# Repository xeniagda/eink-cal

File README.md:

# eink-cal

e-ink calendar based on the *esp32-wroom32* and the waveshare *7.3inch e-Paper HAT (F)*

## file structure

* `./bridge_pcb/`: kicad project for the PCB
* `./eink_bridge/`: esp32-idf project for the WiFi-controller for the display
* `./case.FCStd`: freecad project modelling the 3d-printable chassis for the project
* `./cal_render/`: python code to render the calendar

## needed files

the file `./eink_bridge/main/wifi_creds.h` should be filled in with the following

```c

#ifndef wifi_creds_h_INCLUDED
#define wifi_creds_h_INCLUDED

#define WIFI_SSID "WIFI network SSID here"
#define WIFI_PASSWORD "WIFI network password"
static const char *REMOTE_IP = "IP of computer running cal_render";
static const int REMOTE_PORT = port of the above;

#endif // wifi_creds_h_INCLUDED
```

the file `./cal_render/secrets.toml` contains all calendars to be shown

```toml
[[calendar]]
# hemma
is_caldav = true # true for caldav, false for ical/http
username = "caldav username"
password = "caldav password"
url = "caldav URL"
color1 = "primary color" # one of BLACK, WHITE, BLUE, ORANGE, GREEN, RED, PURPLE
color2 = "secondary color"
```

## credits

font packaged and used is [ultlf](https://github.com/ultlang/ultlf) by emma ultlang. all parts of `./cal_render/ultlf` are re-released under the same SIL open font license.

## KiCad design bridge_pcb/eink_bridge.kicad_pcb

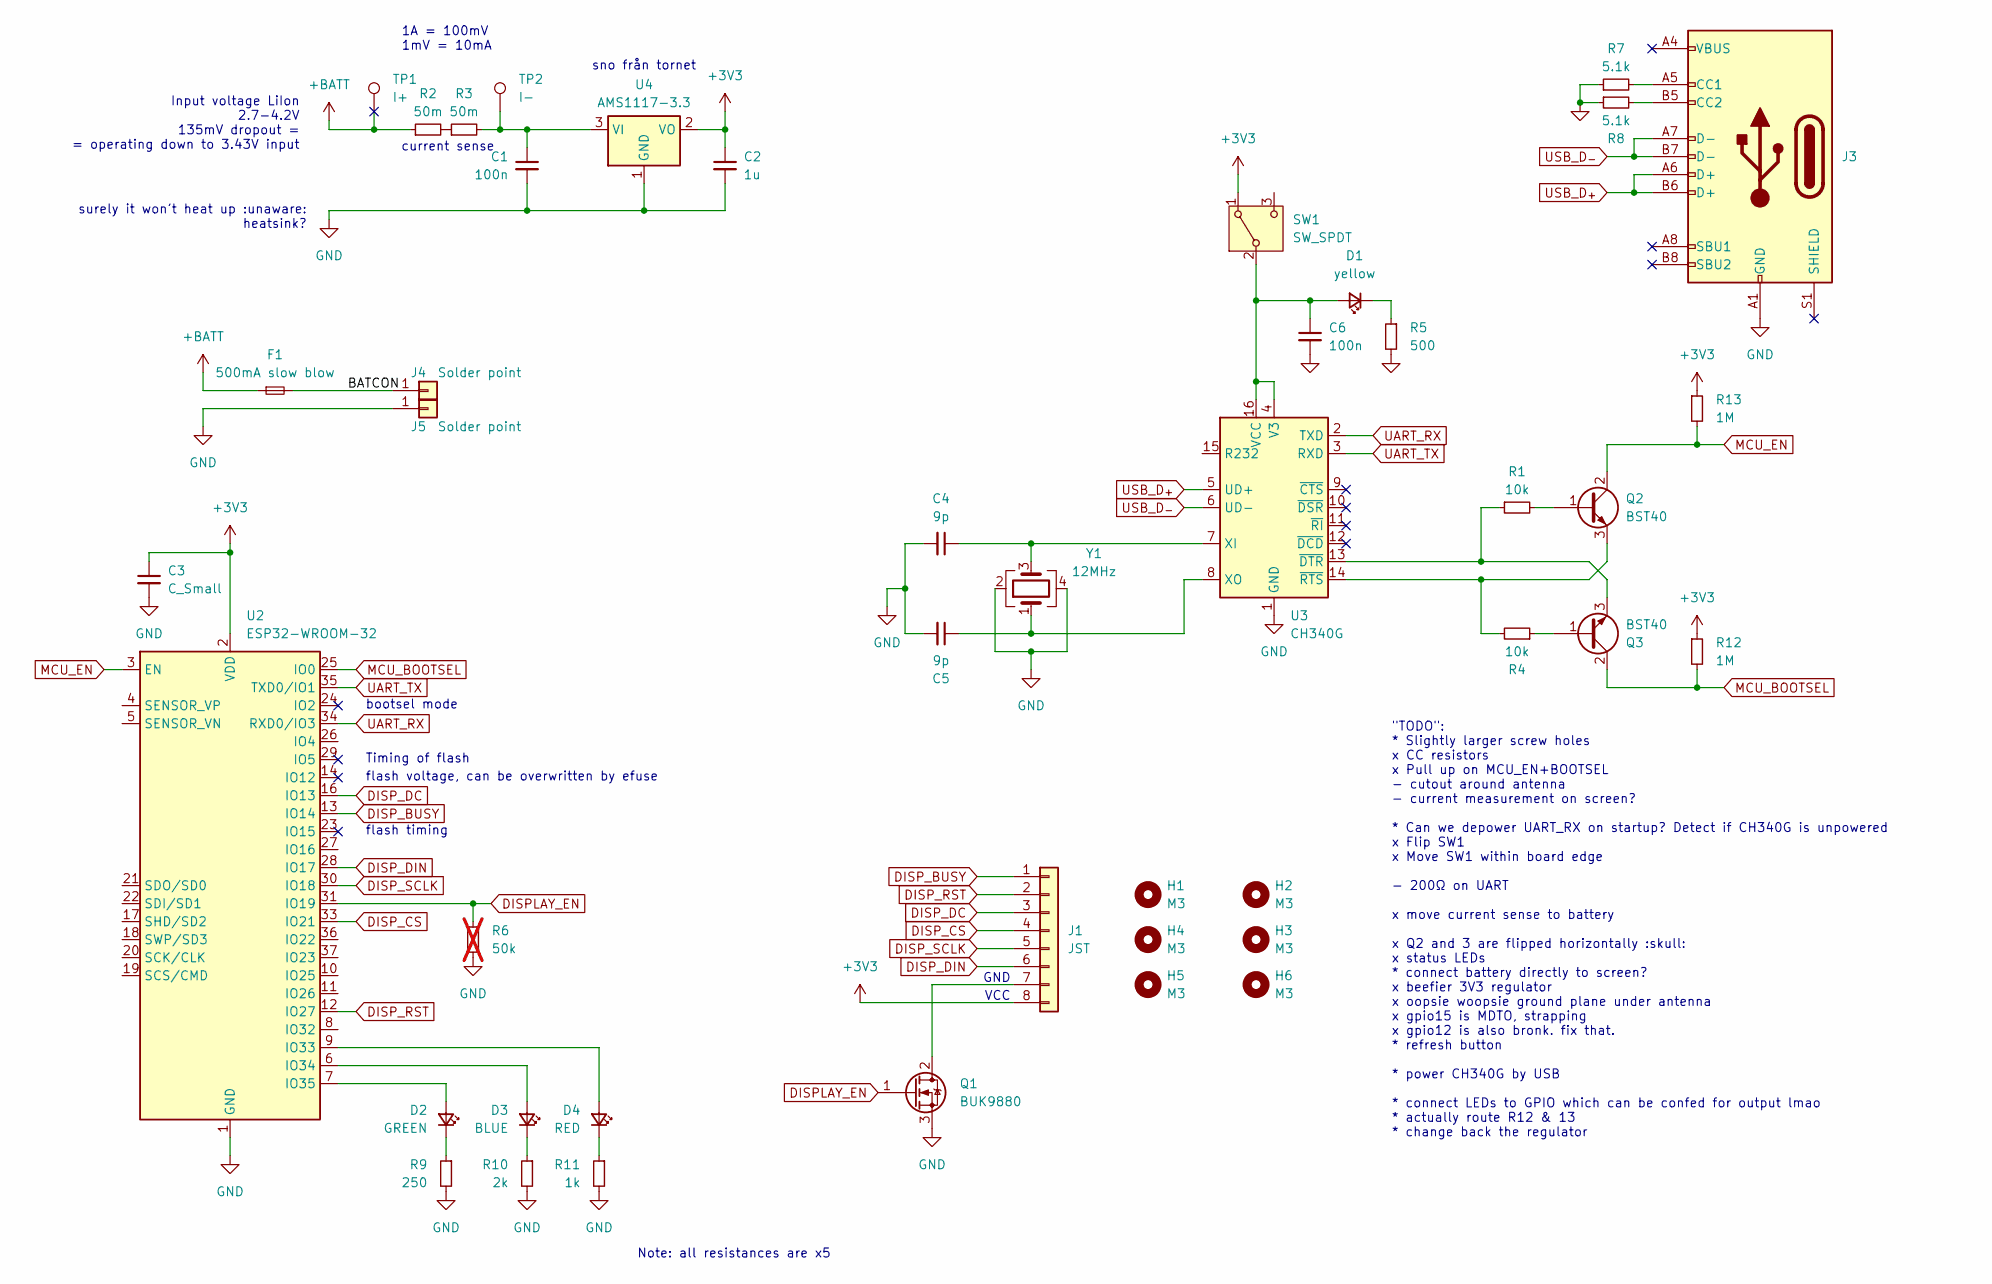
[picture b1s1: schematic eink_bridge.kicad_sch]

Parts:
C1, C6: 100n; C_0603_1608Metric_Pad1.08x0.95mm_HandSolder
C2: 1u; C_0603_1608Metric_Pad1.08x0.95mm_HandSolder
C3: C_Small; C_0603_1608Metric_Pad1.08x0.95mm_HandSolder
C4, C5: 9p; C_0603_1608Metric_Pad1.08x0.95mm_HandSolder
D1: yellow; D_0603_1608Metric_Pad1.05x0.95mm_HandSolder
D2: GREEN; LED_0603_1608Metric_Pad1.05x0.95mm_HandSolder
D3: BLUE; LED_0603_1608Metric_Pad1.05x0.95mm_HandSolder
D4: RED; LED_0603_1608Metric_Pad1.05x0.95mm_HandSolder
F1: 500mA slow blow; Fuseholder_Cylinder-5x20mm_Schurter_OGN-SMD_Horizontal_Open
H1, H2, H3, H4, H5, H6: M3; MountingHole_3.2mm_M3
J1: JST; JST_PH_B8B-PH-SM4-TB_1x08-1MP_P2.00mm_Vertical
J3: USB_C_Receptacle_USB2.0_16P; USB_C_Receptacle_GCT_USB4110
J4, J5: Solder point; TestPoint_Keystone_5019_Minature
Q1: BUK9880; SOT-223-3_TabPin2
Q2, Q3: BST40; SOT-89-3_Handsoldering
R1, R4: 10k; R_0603_1608Metric_Pad0.98x0.95mm_HandSolder
R2, R3: 50m; R_0805_2012Metric_Pad1.20x1.40mm_HandSolder
R5: 500; R_0603_1608Metric_Pad0.98x0.95mm_HandSolder
R6: 50k; R_0603_1608Metric_Pad0.98x0.95mm_HandSolder; not fitted
R7, R8: 5.1k; R_0603_1608Metric_Pad0.98x0.95mm_HandSolder
R9: 250; R_0603_1608Metric_Pad0.98x0.95mm_HandSolder
R10: 2k; R_0603_1608Metric_Pad0.98x0.95mm_HandSolder
R11: 1k; R_0603_1608Metric_Pad0.98x0.95mm_HandSolder
R12, R13: 1M
SW1: SW_SPDT; PinHeader_1x03_P2.54mm_Horizontal
TP1: I+; TestPoint_Bridge_Pitch3.81mm_Drill1.3mm
TP2: I-; TestPoint_Bridge_Pitch3.81mm_Drill1.3mm
U2: ESP32-WROOM-32
U3: CH340G; SOIC-16_3.9x9.9mm_P1.27mm
U4: AMS1117-3.3; SOT-223-3_TabPin2
Y1: 12MHz; Crystal_SMD_3225-4Pin_3.2x2.5mm_HandSoldering

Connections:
+3V3: C2.1, C3.1, J1.8, R12.1, R13.1, SW1.1 (A), U2.2 (VDD), U4.2 (VO)
+BATT: F1.1, R2.1, TP1.1
/BATCON: F1.2, J4.1
DISPLAY_EN: Q1.1 (G), R6.1, U2.31 (IO19)
DISP_BUSY: J1.1, U2.13 (IO14)
DISP_CS: J1.4, U2.33 (IO21)
DISP_DC: J1.3, U2.16 (IO13)
DISP_DIN: J1.6, U2.28 (IO17)
DISP_RST: J1.2, U2.12 (IO27)
DISP_SCLK: J1.5, U2.30 (IO18)
GND: C1.2, C2.2, C3.2, C4.2, C5.2, C6.2, J3.A1 (GND), J3.A12 (GND), J3.B1 (GND), J3.B12 (GND), J5.1, Q1.3 (S), R5.2, R6.2, R7.1, R8.1, R9.2, R10.2, R11.2, U2.1 (GND), U2.15 (GND), U2.38 (GND), U2.39 (GND), U3.1 (GND), U4.1 (GND), Y1.2, Y1.4
MCU_BOOTSEL: Q3.2 (C), R12.2, U2.25 (IO0)
MCU_EN: Q2.2 (C), R13.2, U2.3 (EN)
unnamed: C6.1, D1.2 (A), SW1.2 (B), U3.4 (V3), U3.16 (VCC)
unnamed: D1.1 (K), R5.1
unnamed: D2.2 (A), U2.7 (IO35)
unnamed: D2.1 (K), R9.1
unnamed: D3.2 (A), U2.6 (IO34)
unnamed: D3.1 (K), R10.1
unnamed: D4.2 (A), U2.9 (IO33)
unnamed: D4.1 (K), R11.1
unnamed: J1.7, Q1.2 (D)
unnamed: J3.A5 (CC1), R7.2
unnamed: J3.B5 (CC2), R8.2
unnamed: Q2.1 (B), R1.2
unnamed: Q2.3 (E), R4.2, U3.14 (~RTS)
unnamed: Q3.1 (B), R4.1
unnamed: Q3.3 (E), R1.1, U3.13 (~DTR)
unnamed: R2.2, R3.1
unnamed: C4.1, U3.7 (XI), Y1.3
unnamed: C5.1, U3.8 (XO), Y1.1
unnamed: C1.1, R3.2, TP2.1, U4.3 (VI)
UART_RX: U2.34 (RXD0/IO3), U3.2 (TXD)
UART_TX: U2.35 (TXD0/IO1), U3.3 (RXD)
USB_D_{+}: J3.A6 (D+), J3.B6 (D+), U3.5 (UD+)
USB_D_{-}: J3.A7 (D-), J3.B7 (D-), U3.6 (UD-)

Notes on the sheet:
GND
1A = 100mV 1mV = 10mA
VCC
current sense
flash timing
surely it won't heat up :unaware: heatsink?
sno från tornet
bootsel mode
"TODO": * Slightly larger screw holes x CC resistors x Pull up on MCU_EN+BOOTSEL - cutout around antenna - current measurement on screen? * Can we depower UART_RX on startup? Detect if CH340G is unpowered x Flip SW1 x Move SW1 within board edge - 200Ω on UART x move current sense to battery x Q2 an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
Note: all resistances are x5
flash voltage, can be overwritten by efuse
Timing of flash
Input voltage LiIon 2.7-4.2V 135mV dropout = = operating down to 3.43V input

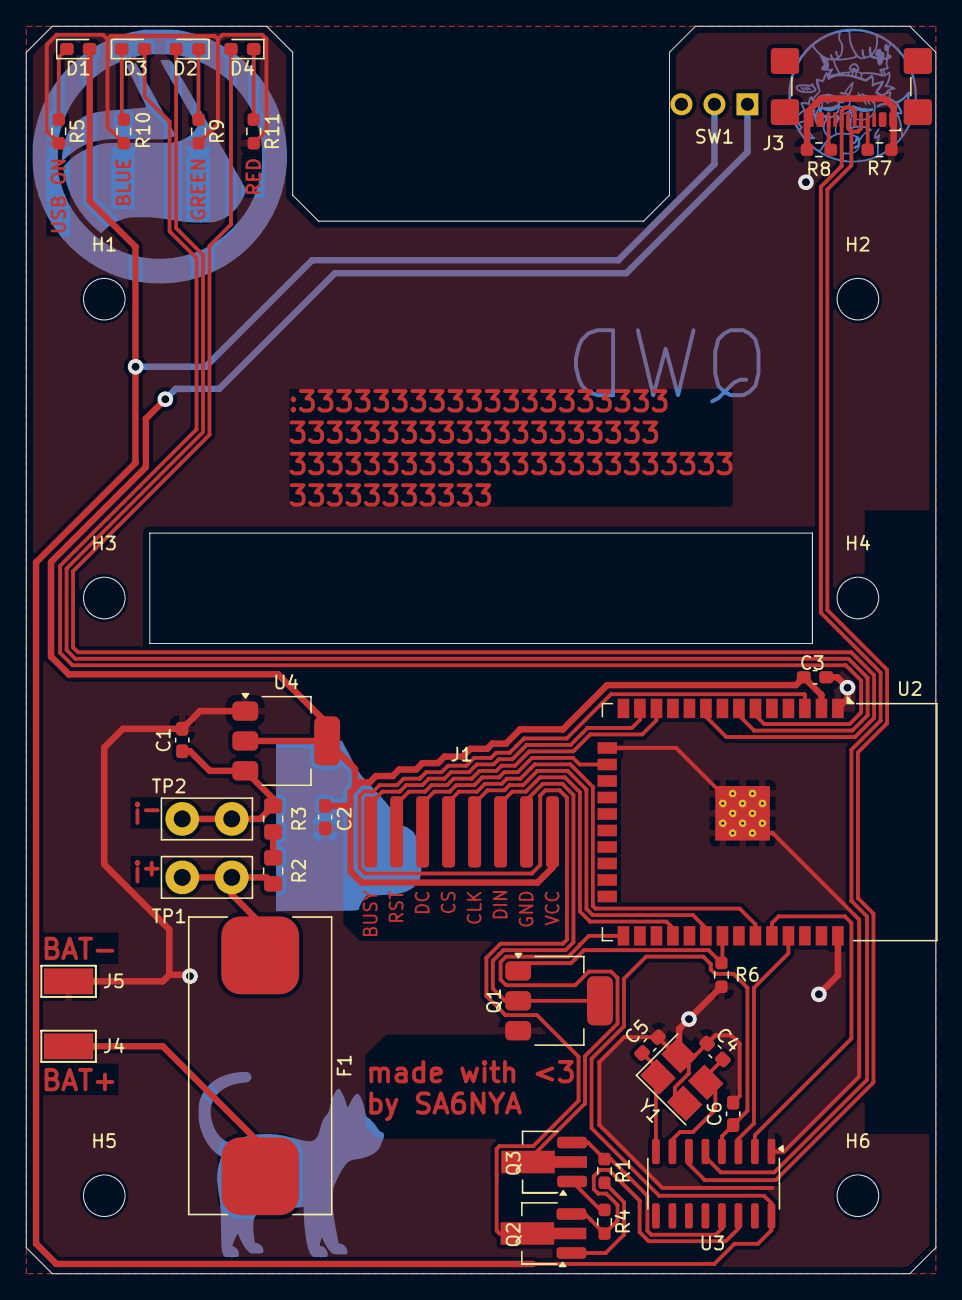
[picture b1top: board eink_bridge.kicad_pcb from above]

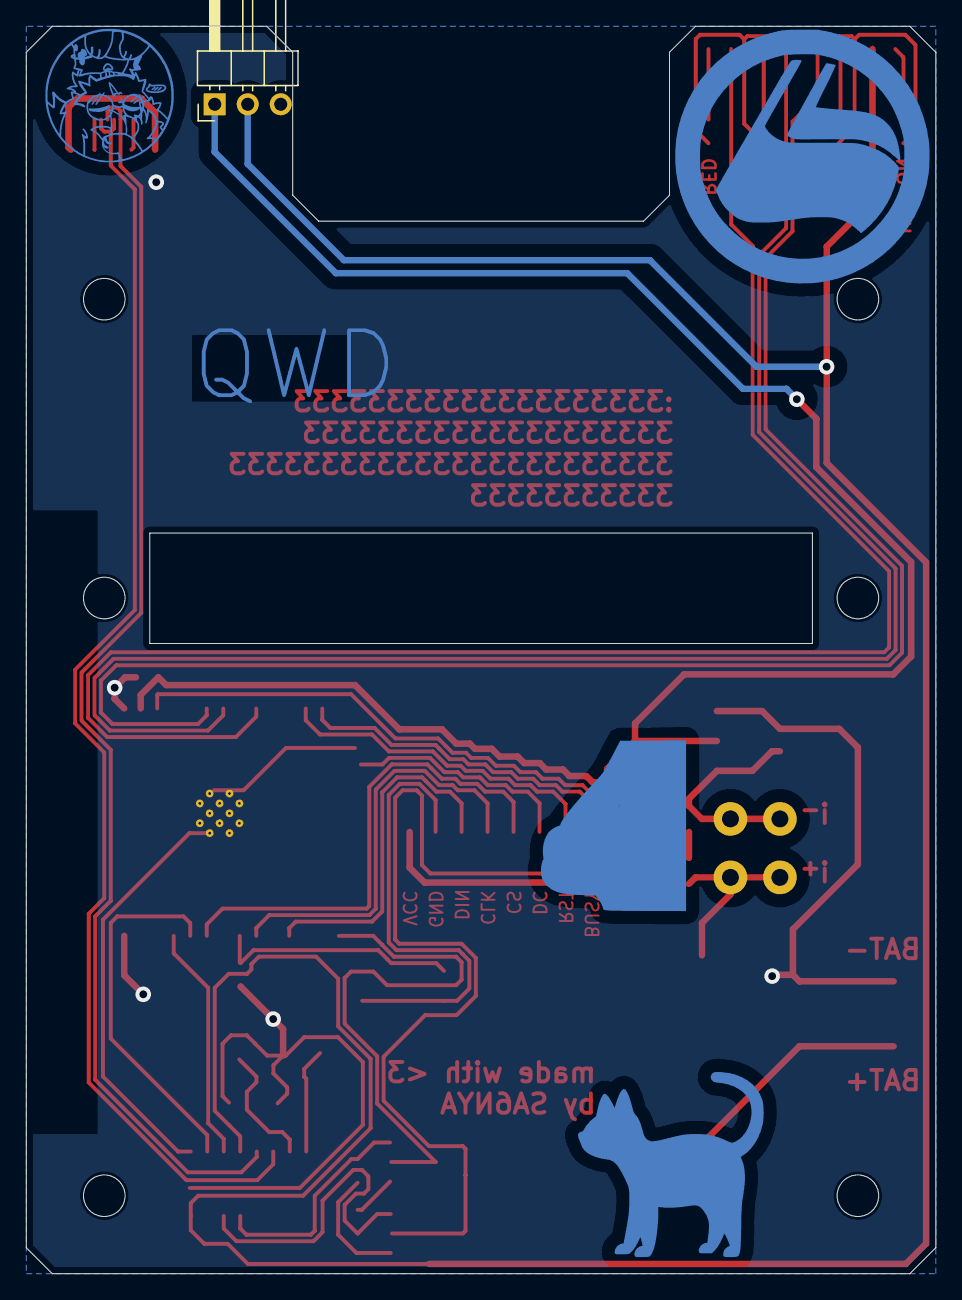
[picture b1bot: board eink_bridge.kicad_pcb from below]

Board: 2 copper layers, 70.0 x 96.0 mm, 44 parts (3 on the bottom side), 36 nets.

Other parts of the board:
Ref**: Val**; t42
Ref**#2: Val**; furry-antifa-20mm

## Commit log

2025-04-23 readme
2025-04-23 move to python313
2025-04-23 make all paths relative
2025-04-23 derivation for cal_render
2025-04-23 move secrets file to argument
2025-05-23 clean up timeedit_parse
2025-05-23 make TE_COURSE a bit more lenient&
